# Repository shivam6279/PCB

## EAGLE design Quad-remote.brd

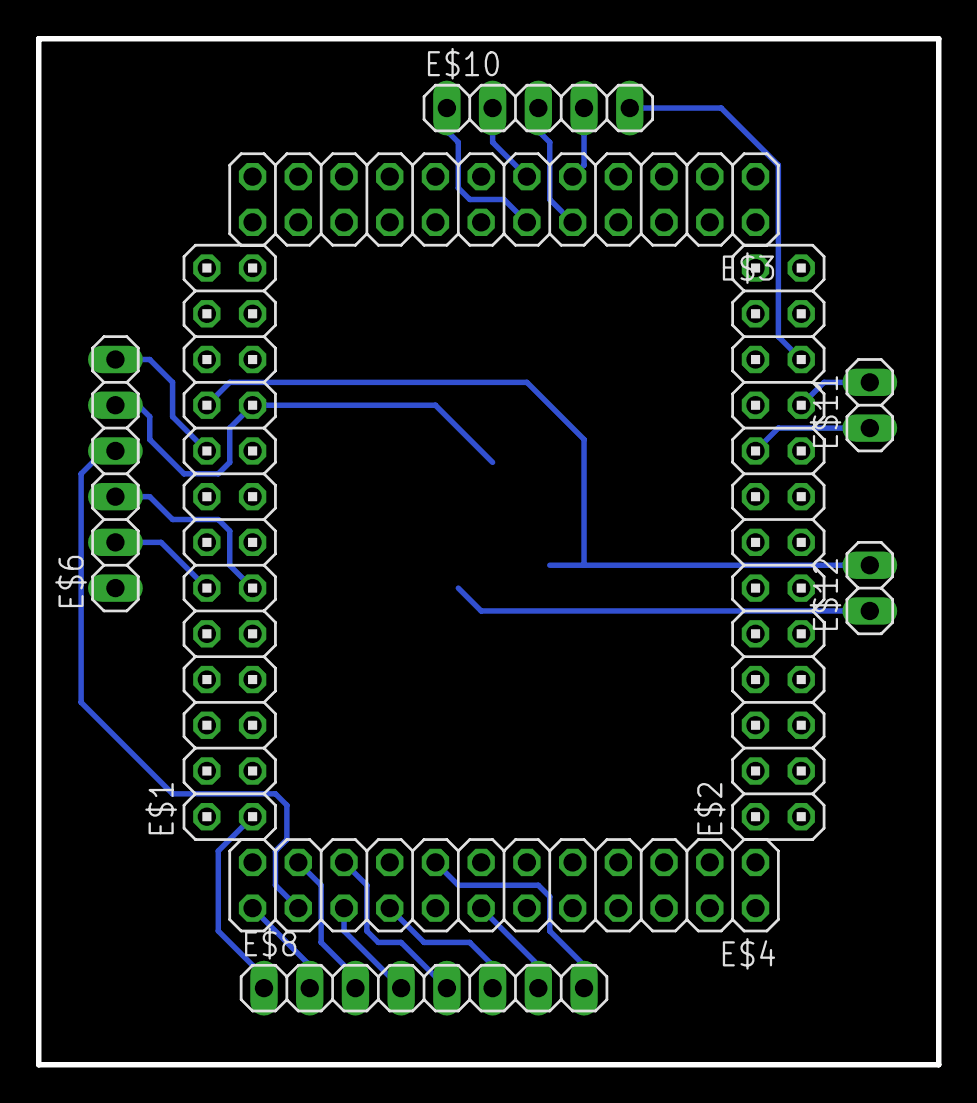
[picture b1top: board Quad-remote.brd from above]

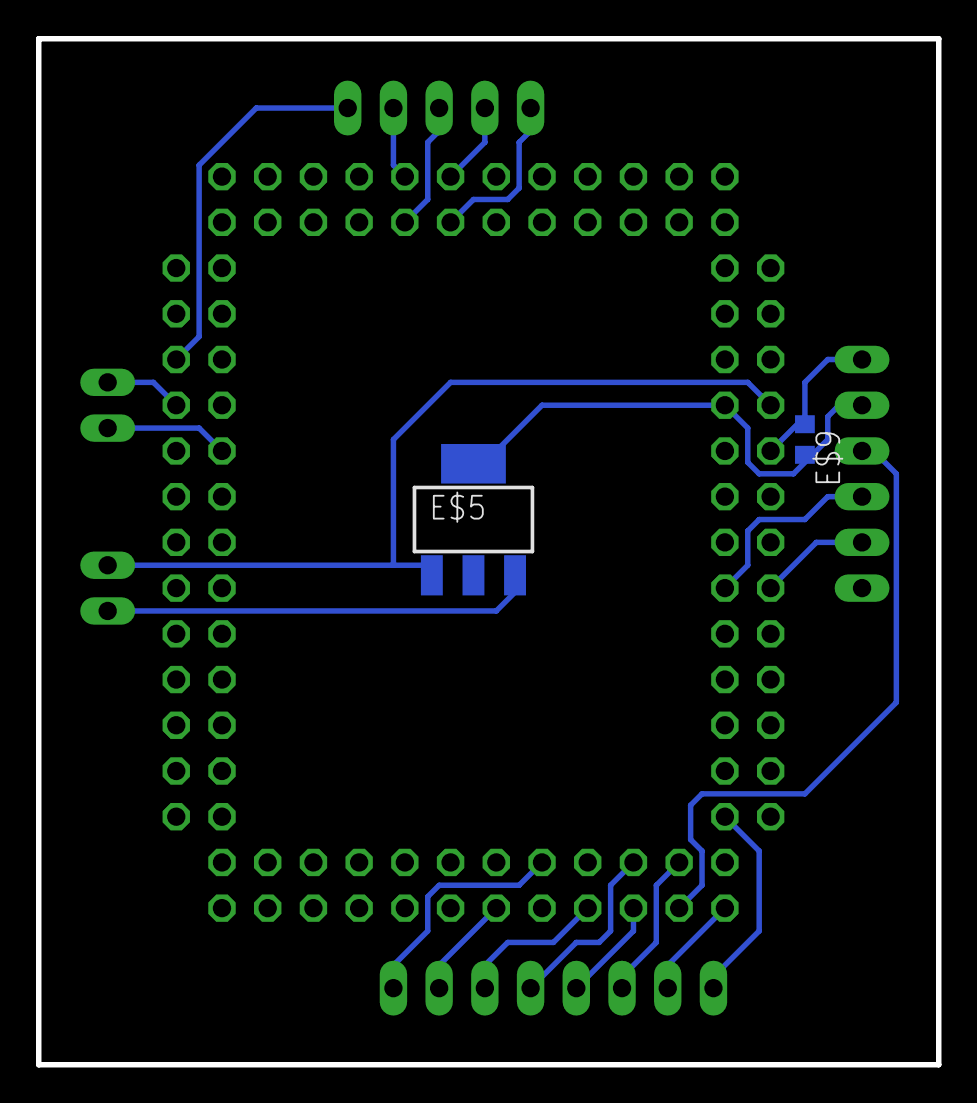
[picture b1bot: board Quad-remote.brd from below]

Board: 2 copper layers, 50.0 x 57.0 mm, 11 parts (2 on the bottom side), 20 nets.

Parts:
E$1, E$2: 2X13
E$3, E$4: 2X12
E$5: SOT223
E$6: 1X06
E$8: 1X08
E$9: R0603
E$10: 1X05
E$11, E$12: 1X02

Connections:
S$20: E$1.20, E$12.2
S$21: E$1.19, E$6.5
S$22: E$1.18, E$6.6
S$23: E$1.12, E$6.2
S$24: E$1.11, E$6.3
S$25: E$1.1, E$8.1
S$26: E$4.24, E$8.2
S$27: E$4.21, E$8.3
S$28: E$4.19, E$8.5
S$29: E$4.20, E$8.4
S$30: E$4.18, E$8.6
S$31: E$4.14, E$8.7
S$32: E$4.15, E$8.8
S$34: E$2.21, E$10.5
S$36: E$3.9, E$10.4
S$37: E$3.10, E$10.3
S$38: E$3.11, E$10.2
S$39: E$3.12, E$10.1
S$41: E$2.18, E$11.1
S$43: E$4.22, E$6.4

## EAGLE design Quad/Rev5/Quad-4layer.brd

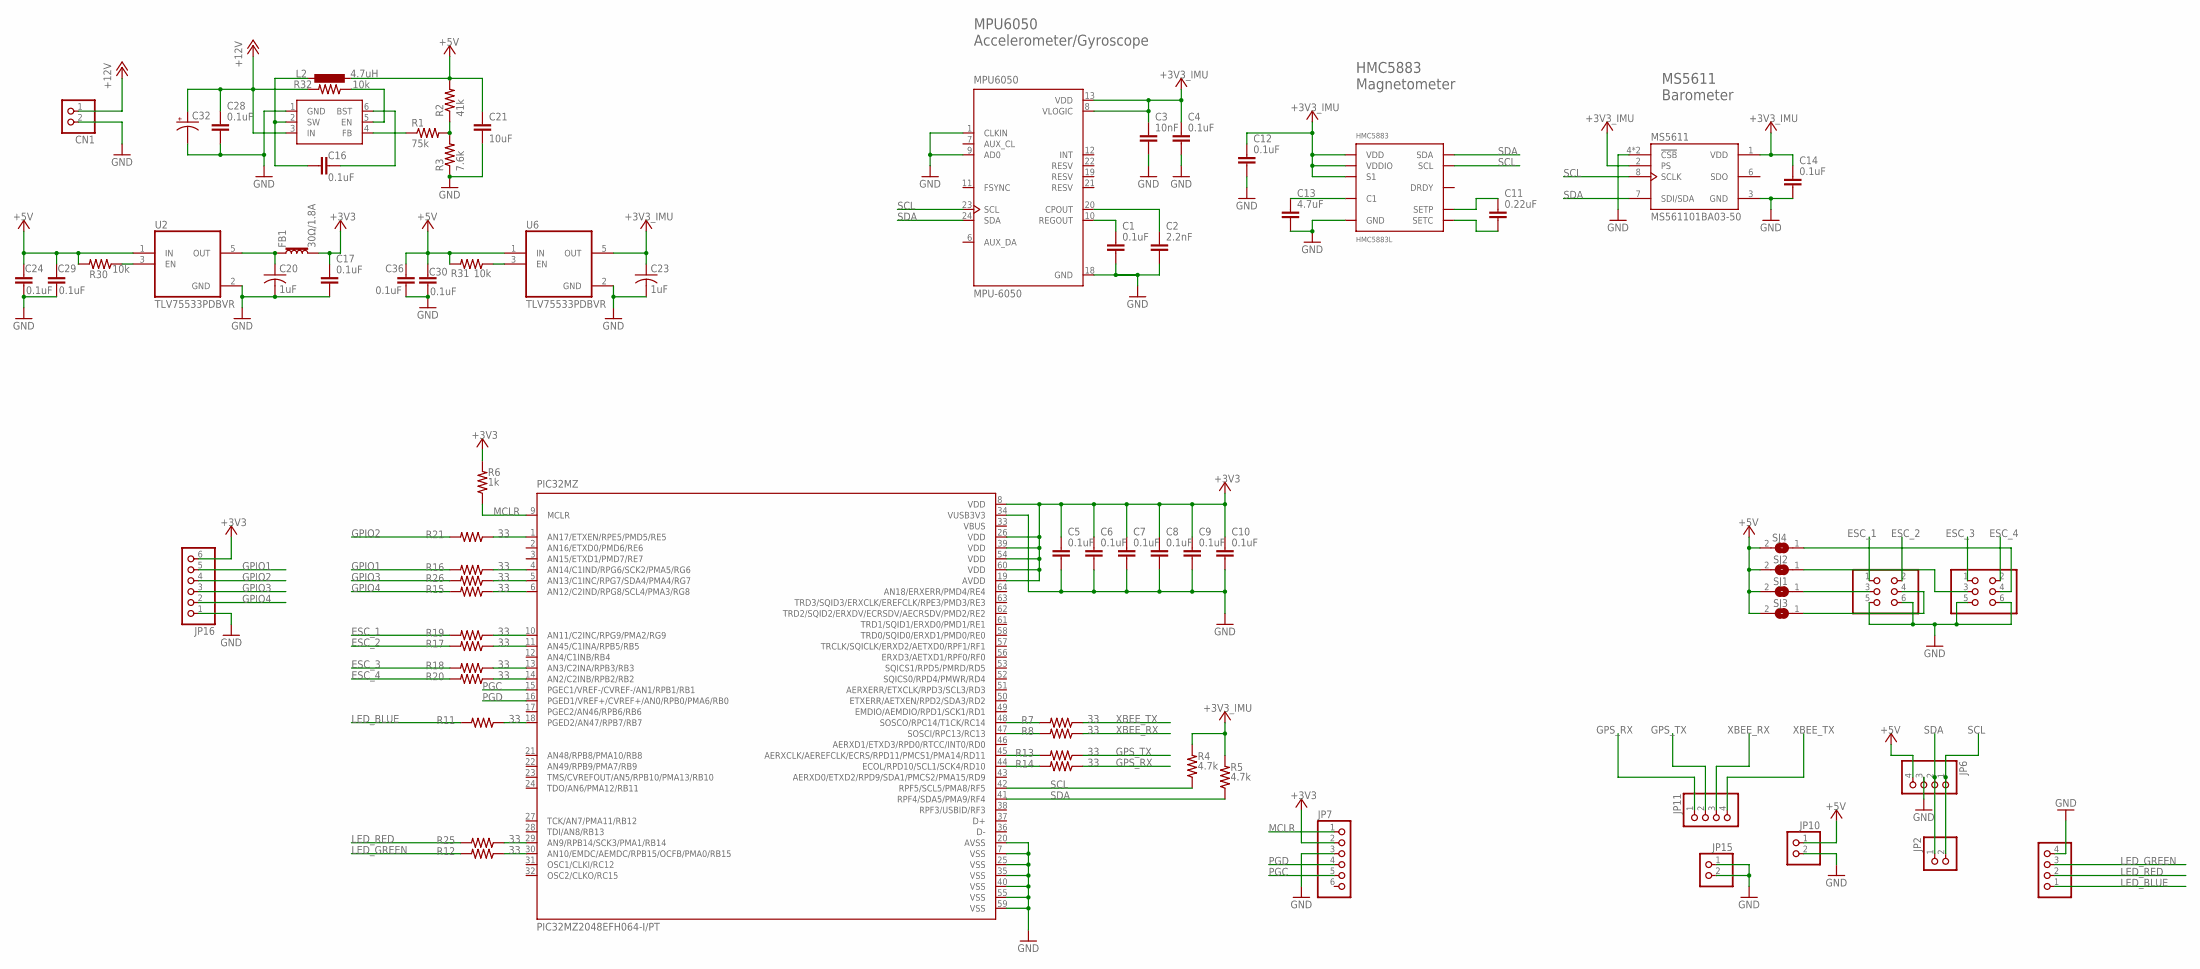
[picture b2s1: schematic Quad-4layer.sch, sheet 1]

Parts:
C1, C4, C5, C6, C7, C8, C9, C10, C12, C14, C16, C17, C24, C28, C29, C30, C36: 0.1uF; C0603
C2: 2.2nF; C0603
C3: 10nF; C0603
C11: 0.22uF; C0603
C13: 4.7uF; C0603
C20, C23: 1uF; C0805
C21: 10uF; C1206
C32: CPOL-US085CS-1AR; 085CS_1AR
CN1: JST_2PIN-THM-RA; JST-PH-2-THM-RA
FB1: 30Ω/1.8A; 0603
HMC5883: HMC5883L; LPCC-16
JP2, JP10, JP15: PINHD-1X2; 1X02
JP4, JP5: PINHD-2X3; 2X03
JP6, JP9, JP11: PINHD-1X4; 1X04
JP7, JP16: PINHD-1X6; 1X06
L2: 4.7uH; L2825P
MPU6050: MPU-6050; QFN50P400X400X95-24N
MS5611: MS561101BA03-50; SON125P500X300X100-8N
PIC32MZ: PIC32MZ2048EFH064-I/PT; QFP50P1200X1200X120-64N
R1: 75k; R0603
R2: 41k; R0603
R3: 7.6k; R0603
R4, R5: 4.7k; R0603
R6: 1k; R0603
R7, R8, R11, R12, R13, R14, R15, R16, R17, R18, R19, R20, R21, R25, R26: 33; R0603
R30, R31, R32: 10k; R0603
SJ1, SJ2, SJ3, SJ4: SJ
U2, U6: TLV75533PDBVR; SOT95P280X145-5N
U$2: AP65211A; SOT95P280X140-6N

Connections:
+3V3: C5.1, C6.1, C7.1, C8.1, C9.1, C10.1, C17.1, FB1.2, JP7.2, JP16.6, PIC32MZ.8 (VDD), PIC32MZ.19 (AVDD), PIC32MZ.26 (VDD), PIC32MZ.39 (VDD), PIC32MZ.54 (VDD), PIC32MZ.60 (VDD), R6.2
+5V: C21.1, C24.1, C29.1, C30.1, C36.1, JP6.4, JP10.1, L2.1, R2.2, R30.2, R31.2, SJ1.2, SJ2.2, SJ3.2, SJ4.2, U2.1 (IN), U6.1 (IN)
+12V: C28.1, C32.+, CN1.1 (2), R32.2, U$2.3 (IN)
ESC_1: JP5.1, R19.2
ESC_2: JP5.2, R17.2
ESC_3: JP4.1, R18.2
ESC_4: JP4.2, R20.2
GND: C1.2, C2.2, C3.2, C4.2, C5.2, C6.2, C7.2, C8.2, C9.2, C10.2, C12.2, C13.2, C14.2, C17.2, C20.2, C21.2, C23.2, C24.2, C28.2, C29.2, C30.2, C32.-, C36.2, CN1.2 (1), HMC5883.9 (GND), HMC5883.11 (GND), JP4.5, JP4.6, JP5.5, JP5.6, JP6.3, JP7.3, JP9.4, JP10.2, JP15.1, JP15.2, JP16.1, MPU6050.1 (CLKIN), MPU6050.9 (AD0), MPU6050.18 (GND), MS5611.3 (GND), MS5611.4 (!CSB), MS5611.5 (!CSB), PIC32MZ.7 (VSS), PIC32MZ.20 (AVSS), PIC32MZ.25 (VSS), PIC32MZ.34 (VUSB3V3), PIC32MZ.35 (VSS), PIC32MZ.40 (VSS), PIC32MZ.55 (VSS), PIC32MZ.59 (VSS), R3.1, U2.2 (GND), U6.2 (GND), U$2.1 (GND)
GPIO1: JP16.5, R16.2
GPIO2: JP16.4, R21.2
GPIO3: JP16.3, R26.2
GPIO4: JP16.2, R15.2
GPS_RX: JP11.1, R14.1
GPS_TX: JP11.2, R13.1
LED_BLUE: JP9.1, R11.2
LED_GREEN: JP9.3, R12.2
LED_RED: JP9.2, R25.2
MCLR: JP7.1, PIC32MZ.9 (MCLR), R6.1
unnamed: C1.1, MPU6050.10 (REGOUT)
unnamed: C2.1, MPU6050.20 (CPOUT)
unnamed: C11.1, HMC5883.8 (SETP)
unnamed: C11.2, HMC5883.12 (SETC)
unnamed: C13.1, HMC5883.10 (C1)
unnamed: C16.1, L2.2, U$2.2 (SW)
unnamed: C16.2, U$2.6 (BST)
unnamed: R1.1, U$2.4 (FB)
unnamed: R1.2, R2.1, R3.2
unnamed: PIC32MZ.48 (SOSCO/RPC14/T1CK/RC14), R7.2
unnamed: PIC32MZ.47 (SOSCI/RPC13/RC13), R8.2
unnamed: PIC32MZ.18 (PGED2/AN47/RPB7/RB7), R11.1
unnamed: PIC32MZ.45 (AERXCLK/AEREFCLK/ECRS/RPD11/PMCS1/PMA14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), R13.2
unnamed: PIC32MZ.44 (ECOL/RPD10/SCL1/SCK4/RD10), R14.2
unnamed: PIC32MZ.29 (AN9/RPB14/SCK3/PMA1/RB14), R25.1
unnamed: PIC32MZ.4 (AN14/C1IND/RPG6/SCK2/PMA5/RG6), R16.1
unnamed: PIC32MZ.1 (AN17/ETXEN/RPE5/PMD5/RE5), R21.1
unnamed: PIC32MZ.11 (AN45/C1INA/RPB5/RB5), R17.1
unnamed: PIC32MZ.13 (AN3/C2INA/RPB3/RB3), R18.1
unnamed: PIC32MZ.10 (AN11/C2INC/RPG9/PMA2/RG9), R19.1
unnamed: PIC32MZ.14 (AN2/C2INB/RPB2/RB2), R20.1
unnamed: JP4.4, SJ4.1
unnamed: PIC32MZ.5 (AN13/C1INC/RPG7/SDA4/PMA4/RG7), R26.1
unnamed: PIC32MZ.6 (AN12/C2IND/RPG8/SCL4/PMA3/RG8), R15.1
unnamed: R31.1, U6.3 (EN)
unnamed: R30.1, U2.3 (EN)
unnamed: PIC32MZ.30 (AN10/EMDC/AEMDC/RPB15/OCFB/PMA0/RB15), R12.1
unnamed: R32.1, U$2.5 (EN)
unnamed: C20.1, FB1.1, U2.5 (OUT)
unnamed: JP5.3, SJ1.1
unnamed: JP4.3, SJ2.1
unnamed: JP5.4, SJ3.1
PGC: JP7.5, PIC32MZ.15 (PGEC1/VREF-/CVREF-/AN1/RPB1/RB1)
PGD: JP7.4, PIC32MZ.16 (PGED1/VREF+/CVREF+/AN0/RPB0/PMA6/RB0)
SCL: HMC5883.1 (SCL), JP2.2, JP6.1, MPU6050.23 (SCL), MS5611.8 (SCLK), PIC32MZ.42 (RPF5/SCL5/PMA8/RF5), R4.1
SDA: HMC5883.16 (SDA), JP2.1, JP6.2, MPU6050.24 (SDA), MS5611.7 (SDI/SDA), PIC32MZ.41 (RPF4/SDA5/PMA9/RF4), R5.1
VBUS: PIC32MZ.33 (VBUS)
VCC: C3.1, C4.1, C12.1, C14.1, C23.1, HMC5883.2 (VDD), HMC5883.4 (S1), HMC5883.13 (VDDIO), MPU6050.8 (VLOGIC), MPU6050.13 (VDD), MS5611.1 (VDD), MS5611.2 (PS), R4.2, R5.2, U6.5 (OUT)
XBEE_RX: JP11.3, R8.1
XBEE_TX: JP11.4, R7.1

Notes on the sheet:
MPU6050 Accelerometer/Gyroscope
HMC5883 Magnetometer
MS5611 Barometer

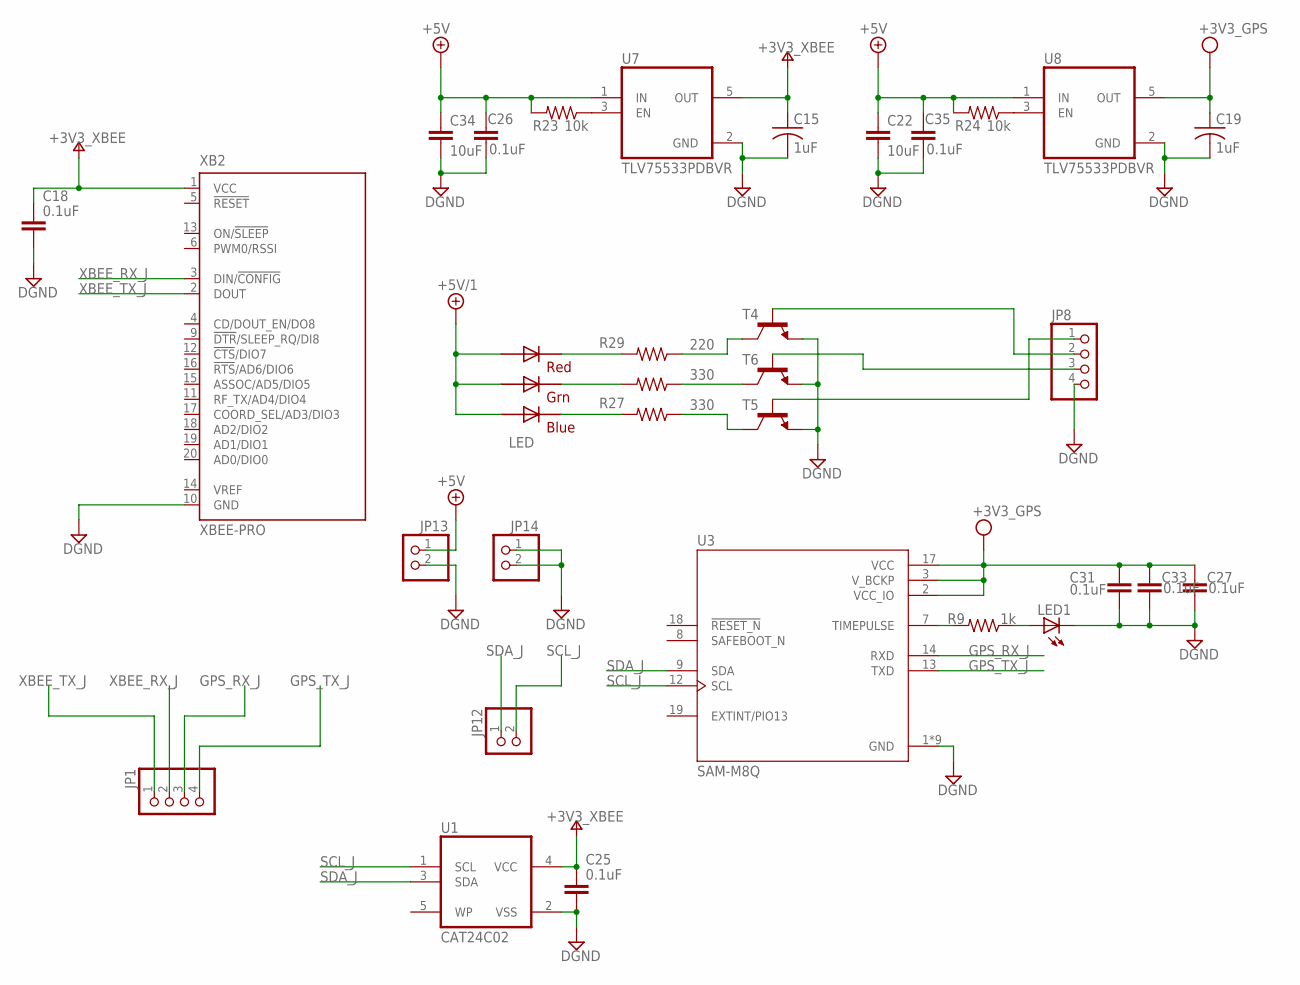
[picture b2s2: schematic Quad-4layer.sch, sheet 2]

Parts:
C15, C19: 1uF; C0805
C18, C25, C26, C27, C31, C33, C35: 0.1uF; C0603
C22, C34: 10uF; C1206
JP1, JP8: PINHD-1X4; 1X04
JP12, JP13, JP14: PINHD-1X2; 1X02
LED: RGBLED5050
LED1: LEDCHIPLED_0603; CHIPLED_0603
R9: 1k; R0603
R23, R24: 10k; R0603
R27, R28: 330; R0603
R29: 220; R0603
T4, T5, T6: -NPN-SOT23-EBC; SOT23-EBC
U1: CAT24C02; SOT95P280X145-5N
U3: SAM-M8Q; XCVR_SAM-M8Q
U7, U8: TLV75533PDBVR; SOT95P280X145-5N
XB2: XBEE-PRO

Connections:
+5V/1: C22.1, C26.1, C34.1, C35.1, JP13.1, LED.1 (GREEN_A), LED.2 (RED_A), LED.3 (BLUE_A), R23.2, R24.2, U7.1 (IN), U8.1 (IN)
DGND: C15.2, C18.2, C19.2, C22.2, C25.2, C26.2, C27.2, C31.2, C33.2, C34.2, C35.2, JP8.4, JP13.2, JP14.1, JP14.2, LED1.C, T4.E, T5.E, T6.E, U1.2 (VSS), U3.1 (GND), U3.4 (GND), U3.5 (GND), U3.6 (GND), U3.10 (GND), U3.11 (GND), U3.15 (GND), U3.16 (GND), U3.20 (GND), U7.2 (GND), U8.2 (GND), XB2.10 (GND)
GPS_RX_J: JP1.3, U3.14 (RXD)
GPS_TX_J: JP1.4, U3.13 (TXD)
LED_BLUE1: JP8.1, T5.B
LED_GREEN1: JP8.2, T4.B
unnamed: LED.5 (RED_C), R29.2
unnamed: LED.6 (GREEN_C), R28.2
unnamed: R9.2, U3.7 (TIMEPULSE)
unnamed: LED.4 (BLUE_C), R27.2
unnamed: LED1.A, R9.1
unnamed: R23.1, U7.3 (EN)
unnamed: R24.1, U8.3 (EN)
unnamed: JP8.3, T6.B
unnamed: R28.1, T6.C
unnamed: R29.1, T4.C
unnamed: R27.1, T5.C
SCL_J: JP12.2, U1.1 (SCL), U3.12 (SCL)
SDA_J: JP12.1, U1.3 (SDA), U3.9 (SDA)
V+: C15.1, C18.1, C25.1, U1.4 (VCC), U7.5 (OUT), XB2.1 (VCC)
VDD: C19.1, C27.1, C31.1, C33.1, U3.2 (VCC_IO), U3.3 (V_BCKP), U3.17 (VCC), U8.5 (OUT)
XBEE_RX_J: JP1.2, XB2.3 (DIN/!CONFIG)
XBEE_TX_J: JP1.1, XB2.2 (DOUT)

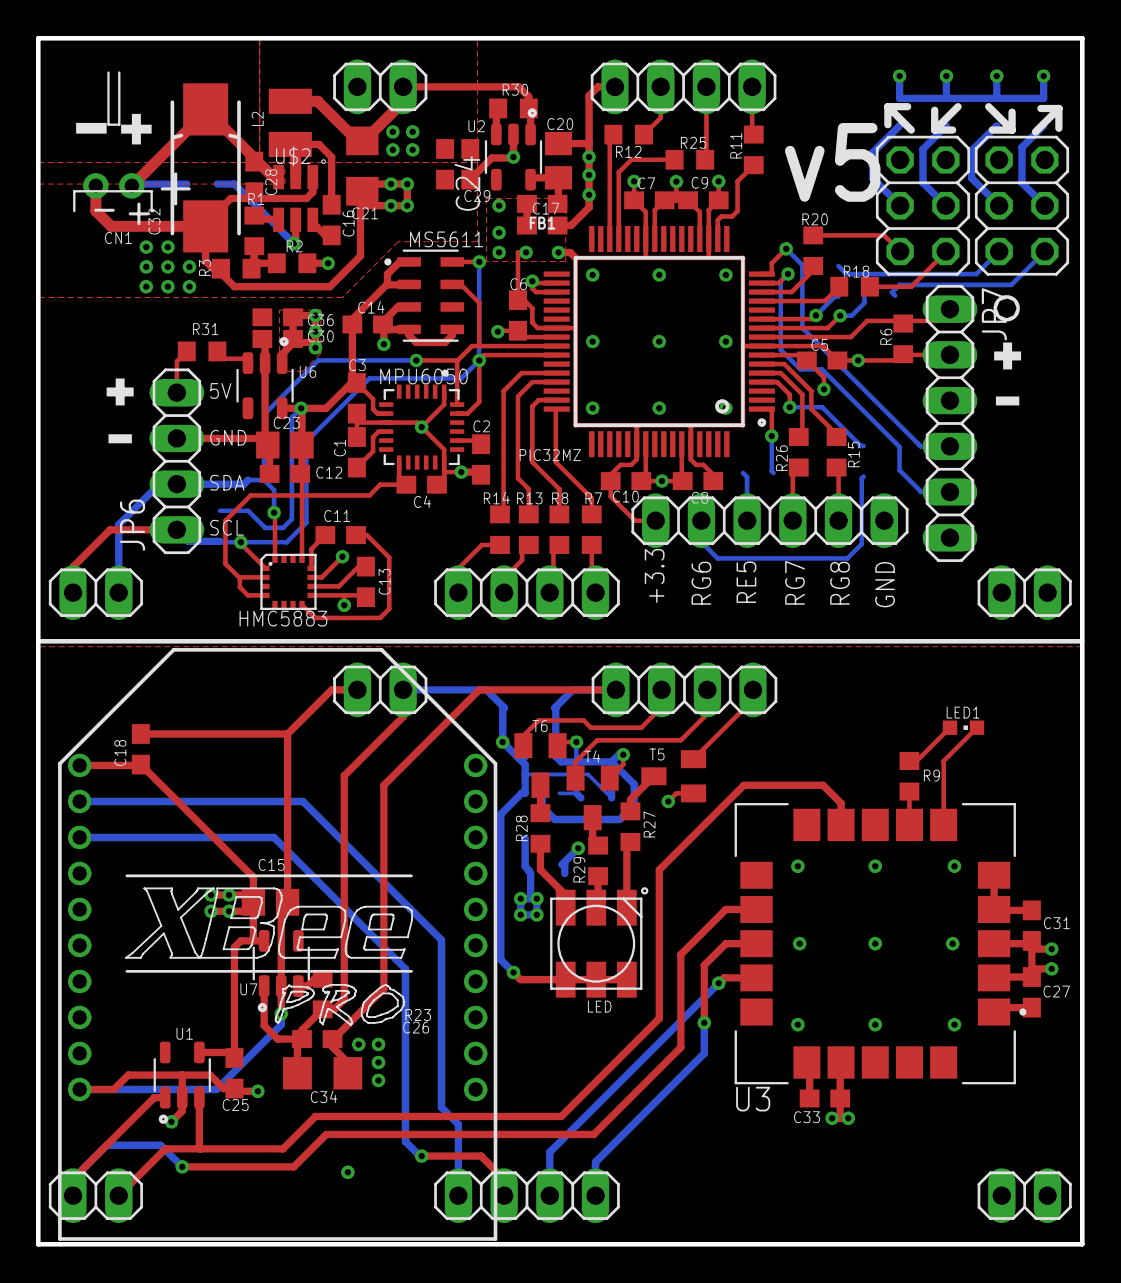
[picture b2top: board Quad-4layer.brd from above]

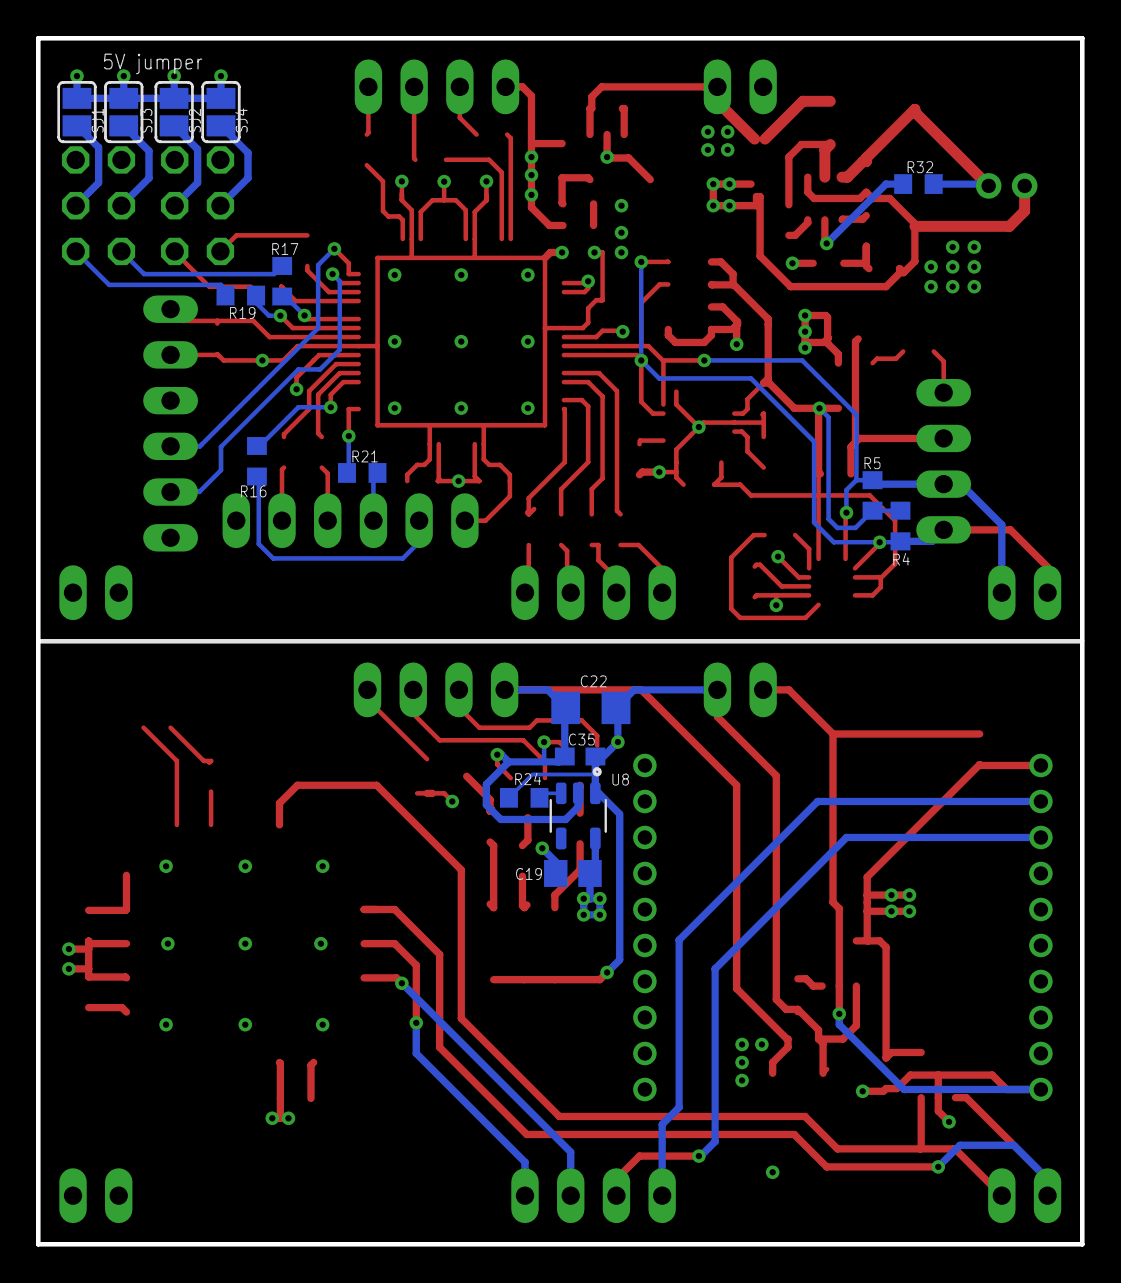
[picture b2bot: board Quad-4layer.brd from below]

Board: 4 copper layers, 58.0 x 67.0 mm, 105 parts (16 on the bottom side), 80 nets.

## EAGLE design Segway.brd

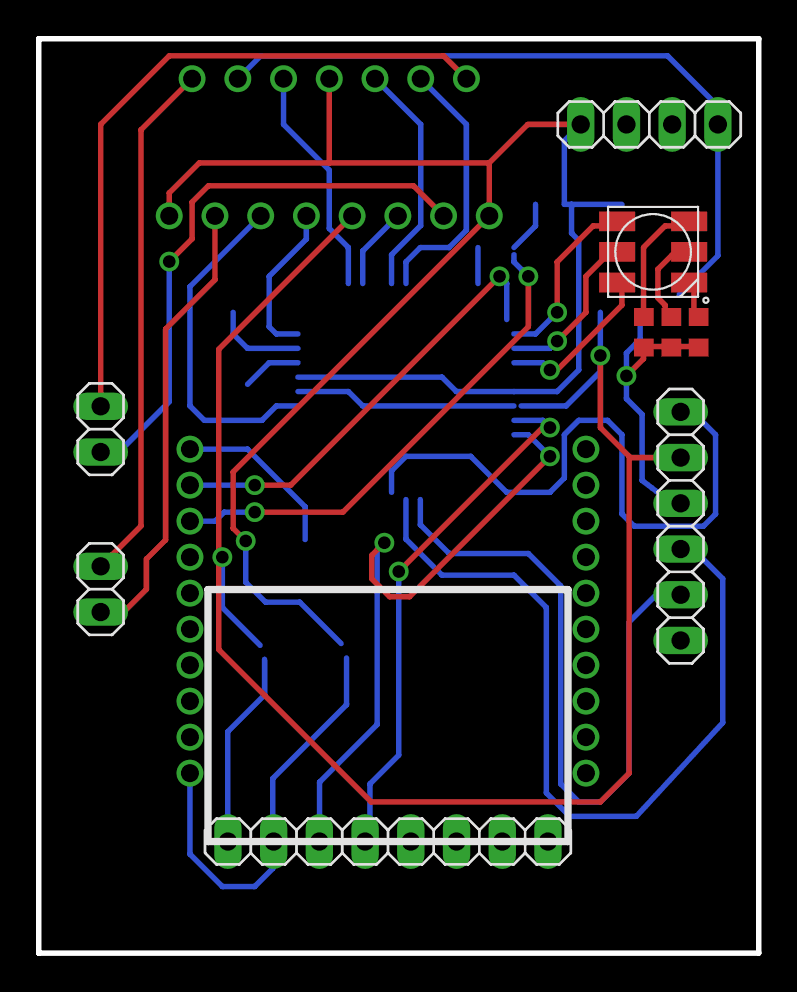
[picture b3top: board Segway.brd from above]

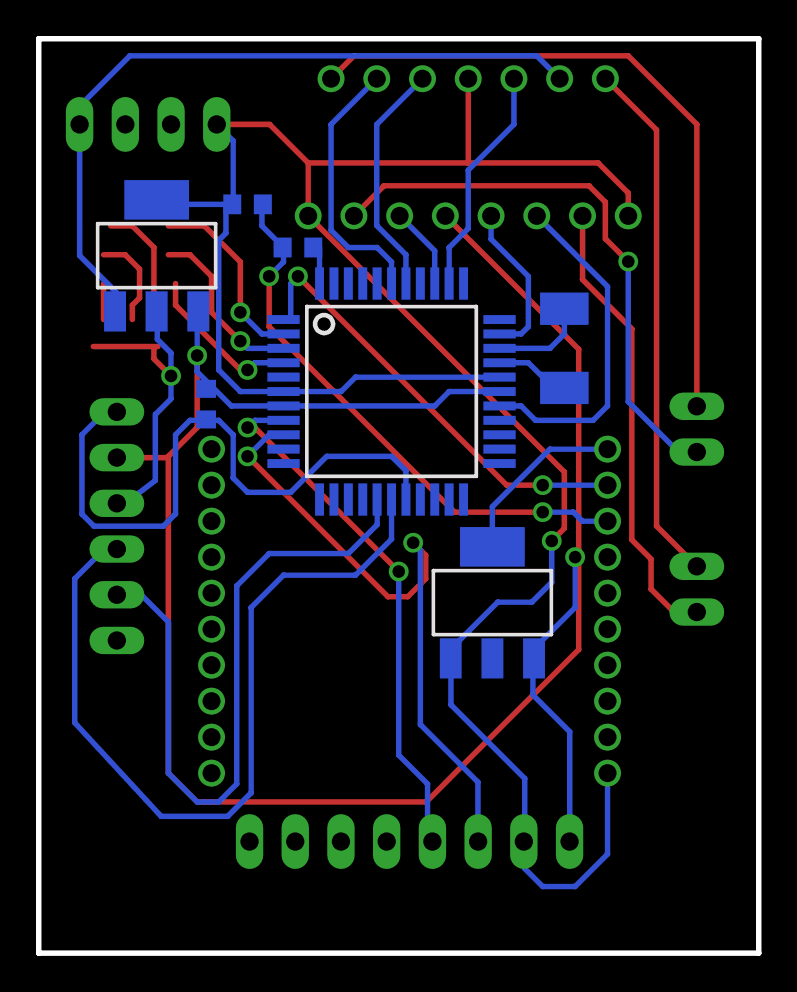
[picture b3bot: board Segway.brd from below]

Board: 2 copper layers, 40.0 x 50.8 mm, 16 parts (7 on the bottom side), 5 nets.

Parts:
E$1: SQFP-S-10X10-44
E$2: RGBLED5050
E$3: 1X06
E$4, E$10: SOT223
E$5, E$7, E$9, E$13, E$14, E$15: R0603
E$6: R2010
E$8: 1X04
E$11, E$12: 1X02
E$16: 1X08

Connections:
S$23: E$1.7, E$1.28
S$29: E$1.17, E$3.3
S$30: E$1.16, E$3.2
S$35: E$1.6, E$1.29, E$8.1
S$41: E$1.2, E$1.3, E$1.4

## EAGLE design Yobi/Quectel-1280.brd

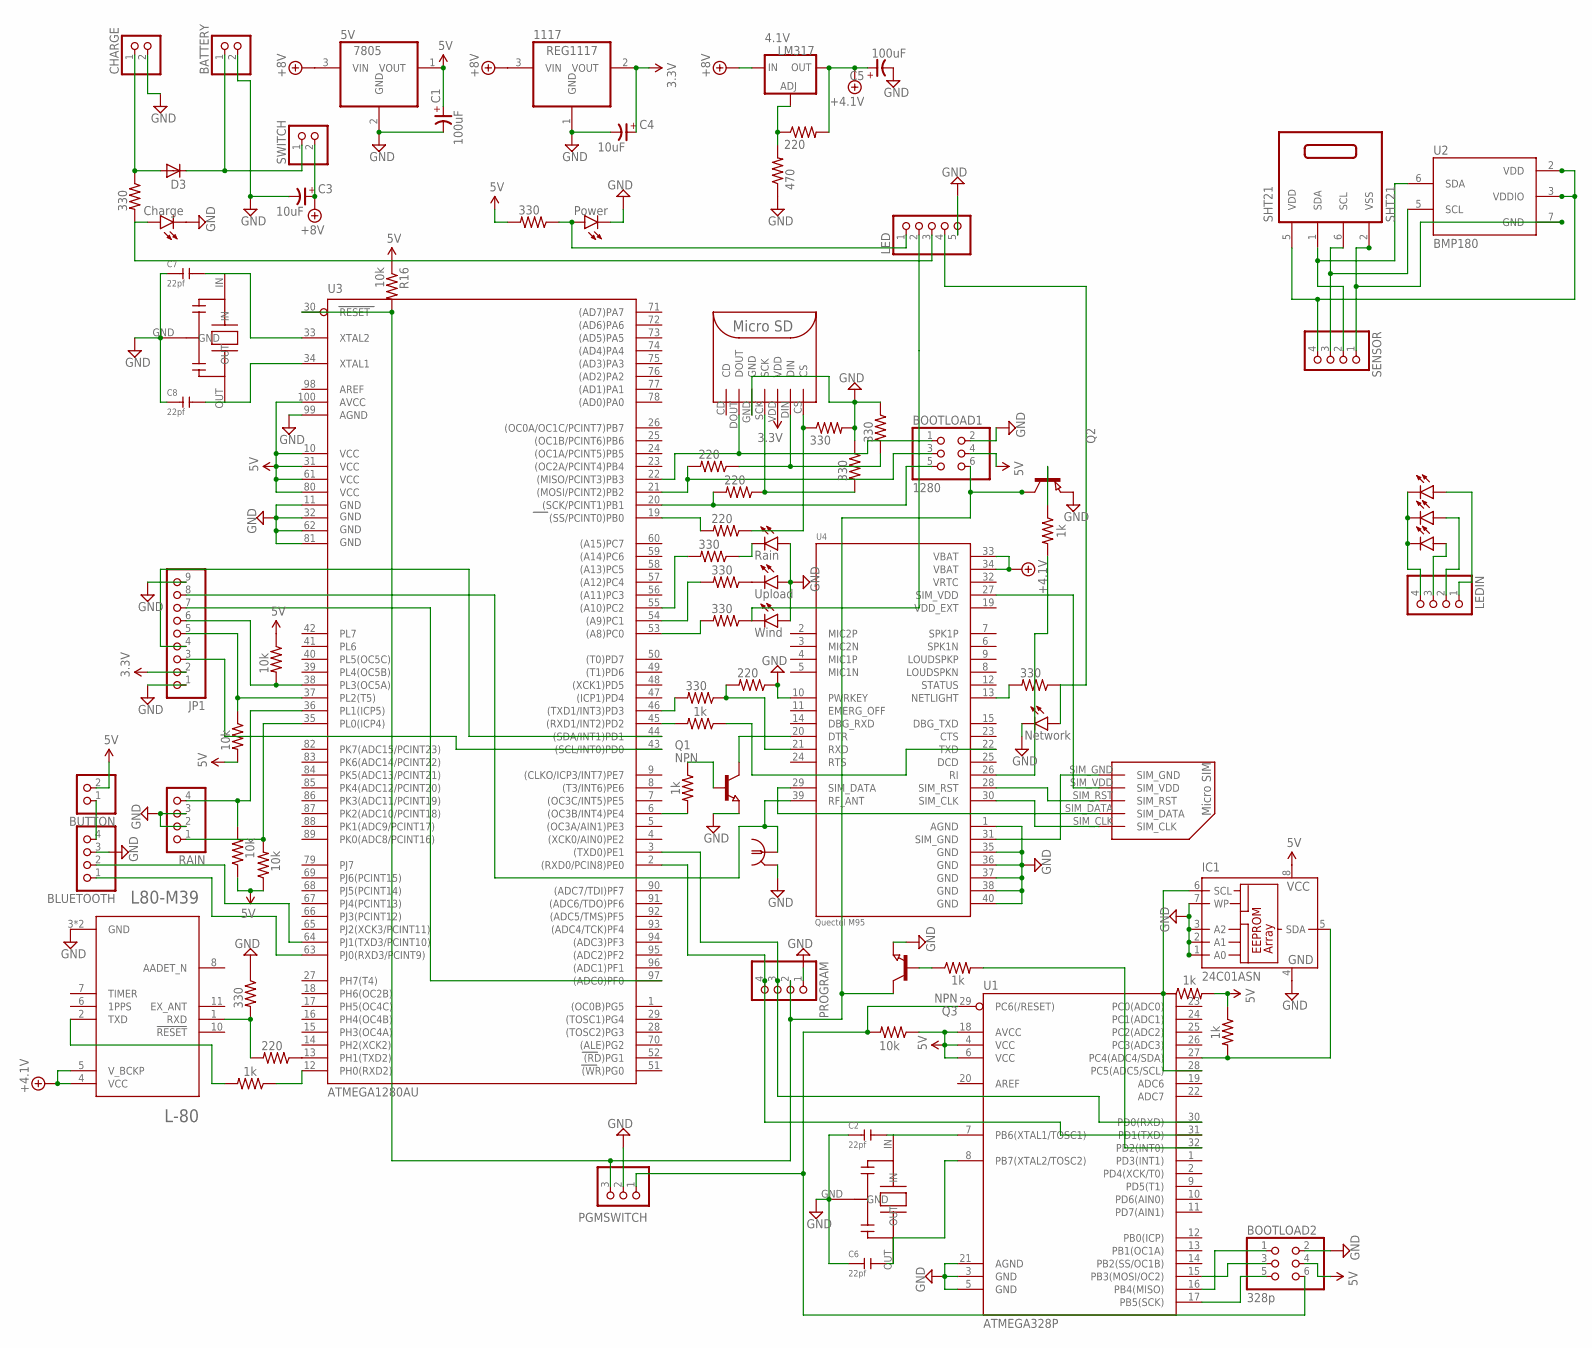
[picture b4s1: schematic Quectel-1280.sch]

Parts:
4.1V: LM317; DPACK
5V: 7805; SOT223; MPN 7805
1117: REG1117; SOT223
ANT: LTI-SASF54GT
BATTERY: PINHD-1X2; 1X02
BLUETOOTH: PINHD-1X4; 1X04
BOOTLOAD1: 1280; 2X03
BOOTLOAD2: 328p; 2X03
BUTTON: PINHD-1X2; 1X02
C1, C5: 100uF; 3528/T
C2, C6, C7, C8: 22pf; C0805
C3, C4: 10uF; 3528/T
CHARGE: PINHD-1X2; 1X02
D1: Charge; LED-1206
D2: Rain; LED-1206
D3: BYS10; SOD106A
D4: Upload; LED-1206
D5: Power; LED-1206
D6: Network; LED-1206
D7: Wind; LED-1206
D8, D9, D10: LED-BLUE1206; LED-1206
IC1: 24C01ASN; SO-08
JP1: PINHD-1X9; 1X09
L-80: L80-M39; QUECTEL_L80-M39
LED: PINHD-1X5; 1X05
LEDIN: PINHD-1X4; 1X04
PGMSWITCH: PINHD-1X3; 1X03
PROGRAM: PINHD-1X4; 1X04
Q1, Q3: NPN; SOT23
Q2: PNP-TRANSISTOR_SOT23; SOT23
R1, R16, R19, R20, R21, R22: 10k; 0805
R2, R3, R5, R13, R15, R30, R31: 1k; 0805
R4, R9, R14, R17, R18, R23, R24, R25, R26, R27, R28: 330; 0805
R6, R7, R8, R10, R12, R29: 220; 0805
R11: 470; 0805
RAIN: PINHD-1X4; 1X04
SENSOR: PINHD-1X4; 1X04
SHT21: SHT21; DFN6/SHT
SWITCH: PINHD-1X2; 1X02
U1: ATMEGA328P; TQFP32-08
U2: BMP180
U3: ATMEGA1280AU; TQFP100
U4: Quectel M95; XCVR_M95
U$1: MICROSD
U$2: MICROSIM
Y1, Y2: CSTCE16M0V53-R0; CFP95P160X100-3N

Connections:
3.3V: 1117.2 (VOUT), C4.+, JP1.2, U$1.VDD
5V: 5V.1 (VOUT), BOOTLOAD1.4, BOOTLOAD2.4, BUTTON.2, C1.+, IC1.8 (VCC), R1.1, R5.1, R16.1, R18.2, R19.1, R20.2, R21.1, R22.1, R30.2, U1.4 (VCC), U1.6 (VCC), U1.18 (AVCC), U3.10 (VCC), U3.31 (VCC1), U3.61 (VCC2), U3.80 (VCC3), U3.100 (AVCC)
+4.1V: 4.1V.4 (OUT), C5.+, L-80.4 (VCC), L-80.5 (V_BCKP), R10.2, U4.33 (VBAT), U4.34 (VBAT)
+8V: 4.1V.3 (IN), 5V.3 (VIN), 1117.3 (VIN), C3.+, SWITCH.2
GND: 5V.2 (GND), 1117.1 (GND), ANT.2, ANT.3 (2), ANT.4 (2), ANT.5 (2), BATTERY.2, BLUETOOTH.3, BOOTLOAD1.2, BOOTLOAD2.2, C1.-, C2.1, C3.-, C4.-, C5.-, C6.1, C7.1, C8.1, CHARGE.2, D1.C, D2.A, D4.A, D5.C, D6.C, D7.A, IC1.1 (A0), IC1.2 (A1), IC1.3 (A2), IC1.4 (GND), IC1.7 (WP), JP1.1, JP1.9, L-80.3 (GND), L-80.12 (GND), LED.5, PGMSWITCH.2, PROGRAM.1, Q1.2 (E), Q2.2 (E), Q3.2 (E), R4.1, R9.1, R11.1, R23.2, R24.1, R29.1, RAIN.2, RAIN.3, U1.3 (GND), U1.5 (GND), U1.21 (AGND), U3.11 (GND), U3.32 (GND1), U3.62 (GND2), U3.81 (GND3), U3.99 (AGND), U4.1 (AGND), U4.10 (PWRKEY), U4.35 (GND), U4.36 (GND), U4.37 (GND), U4.38 (GND), U4.40 (GND), U$1.GND, Y1.GND, Y2.GND
GNDLED: D8.C, D9.C, D10.C, LEDIN.4
GNDSENSOR: SENSOR.1, SHT21.2 (VSS), U2.7 (GND)
unnamed: U4.31 (SIM_GND), U$2.SIM_GND
unnamed: U4.27 (SIM_VDD), U$2.SIM_VDD
unnamed: U4.28 (SIM_RST), U$2.SIM_RST
unnamed: U4.29 (SIM_DATA), U$2.SIM_DATA
unnamed: ANT.1, JP1.8, U4.39 (RF_ANT)
unnamed: U4.30 (SIM_CLK), U$2.SIM_CLK
unnamed: L-80.2 (TXD), R13.2
unnamed: PROGRAM.4, U1.31 (PD1(TXD)), U3.2 ((RXD0/PCIN8)PE0)
unnamed: PROGRAM.3, U1.30 (PD0(RXD)), U3.3 ((TXD0)PE1)
unnamed: R7.1, R24.2, U$1.SCK
unnamed: BOOTLOAD1.1, U3.22 ((MISO/PCINT3)PB3), U$1.DOUT
unnamed: R6.1, R9.2, U$1.DIN
unnamed: C2.2, U1.7 (PB6(XTAL1/TOSC1)), Y1.IN
unnamed: R2.2, U3.6 ((OC3B/INT4)PE4)
unnamed: Q1.1 (B), R2.1
unnamed: BOOTLOAD1.3, R6.2, U3.21 ((MOSI/PCINT2)PB2)
unnamed: BOOTLOAD1.5, R7.2, U3.20 ((SCK/PCINT1)PB1)
unnamed: R3.2, U4.26 (RI)
unnamed: BATTERY.1, D3.K, SWITCH.1
unnamed: R8.2, U3.19 ((SS/PCINT0)PB0)
unnamed: BOOTLOAD2.1, U1.16 (PB4(MISO))
unnamed: BOOTLOAD2.3, U1.15 (PB3(MOSI/OC2))
unnamed: BOOTLOAD2.5, U1.17 (PB5(SCK))
unnamed: C6.2, U1.8 (PB7(XTAL2/TOSC2)), Y1.OUT
unnamed: CHARGE.1, D3.A, R26.1
unnamed: BOOTLOAD2.6, PGMSWITCH.1, R1.2, U1.29 (PC6(/RESET))
unnamed: D1.A, LED.3, R26.2
unnamed: Q2.1 (B), R3.1
unnamed: 4.1V.1 (ADJ), R10.1, R11.2
unnamed: C7.2, U3.33 (XTAL2), Y2.IN
unnamed: C8.2, U3.34 (XTAL1), Y2.OUT
unnamed: D7.C, LED.2, R28.1
unnamed: D4.C, R25.1
unnamed: D2.C, R27.1
unnamed: R8.1, R23.1, U$1.CS
unnamed: R12.1, U3.13 (PH1(TXD2))
unnamed: R13.1, U3.12 (PH0(RXD2))
unnamed: L-80.1 (RXD), R4.2, R12.2
unnamed: R28.2, U3.53 ((A8)PC0)
unnamed: R14.2, U3.46 ((TXD1/INT3)PD3)
unnamed: R15.2, U3.45 ((RXD1/INT2)PD2)
unnamed: R14.1, R29.2, U4.21 (RXD)
unnamed: R15.1, U4.22 (TXD)
unnamed: IC1.5 (SDA), R5.2, U1.27 (PC4(ADC4/SDA))
unnamed: R25.2, U3.54 ((A9)PC1)
unnamed: Q1.3 (C), U4.20 (DTR)
unnamed: BOOTLOAD1.6, PGMSWITCH.3, PROGRAM.2, Q2.3 (C), Q3.3 (C), R16.2, U3.30 (RESET)
unnamed: R27.2, U3.55 ((A10)PC2)
unnamed: IC1.6 (SCL), R30.1, U1.28 (PC5(ADC5/SCL))
unnamed: R17.2, U4.13 (NETLIGHT)
unnamed: D6.A, LED.4, R17.1
unnamed: Q3.1 (B), R31.1
unnamed: JP1.3, U3.43 ((SCL/INT0)PD0)
unnamed: JP1.4, U3.44 ((SDA/INT1)PD1)
unnamed: JP1.5, R20.1, U3.37 (PL2(T5))
unnamed: JP1.6, R19.2, U3.38 (PL3(OC5A))
unnamed: JP1.7, U3.97 ((ADC0)PF0)
unnamed: R21.2, RAIN.4, U3.36 (PL1(ICP5))
unnamed: R22.2, RAIN.1, U3.35 (PL0(ICP4))
unnamed: D5.A, LED.1, R18.1
unnamed: R31.2, U1.32 (PD2(INT0))
unnamed: BLUETOOTH.2, U3.64 (PJ1(TXD3/PCINT10))
unnamed: SENSOR.2, SHT21.1 (SDA), U2.6 (SDA)
unnamed: SENSOR.3, SHT21.6 (SCL), U2.5 (SCL)
unnamed: SENSOR.4, SHT21.5 (VDD), U2.2 (VDD), U2.3 (VDDIO)
unnamed: BLUETOOTH.1, U3.63 (PJ0(RXD3/PCINT9))
unnamed: D10.A, LEDIN.3
unnamed: D8.A, LEDIN.2
unnamed: D9.A, LEDIN.1
unnamed: BLUETOOTH.4, BUTTON.1
VDD_EXT: U4.19 (VDD_EXT)
VRTC: U4.32 (VRTC)

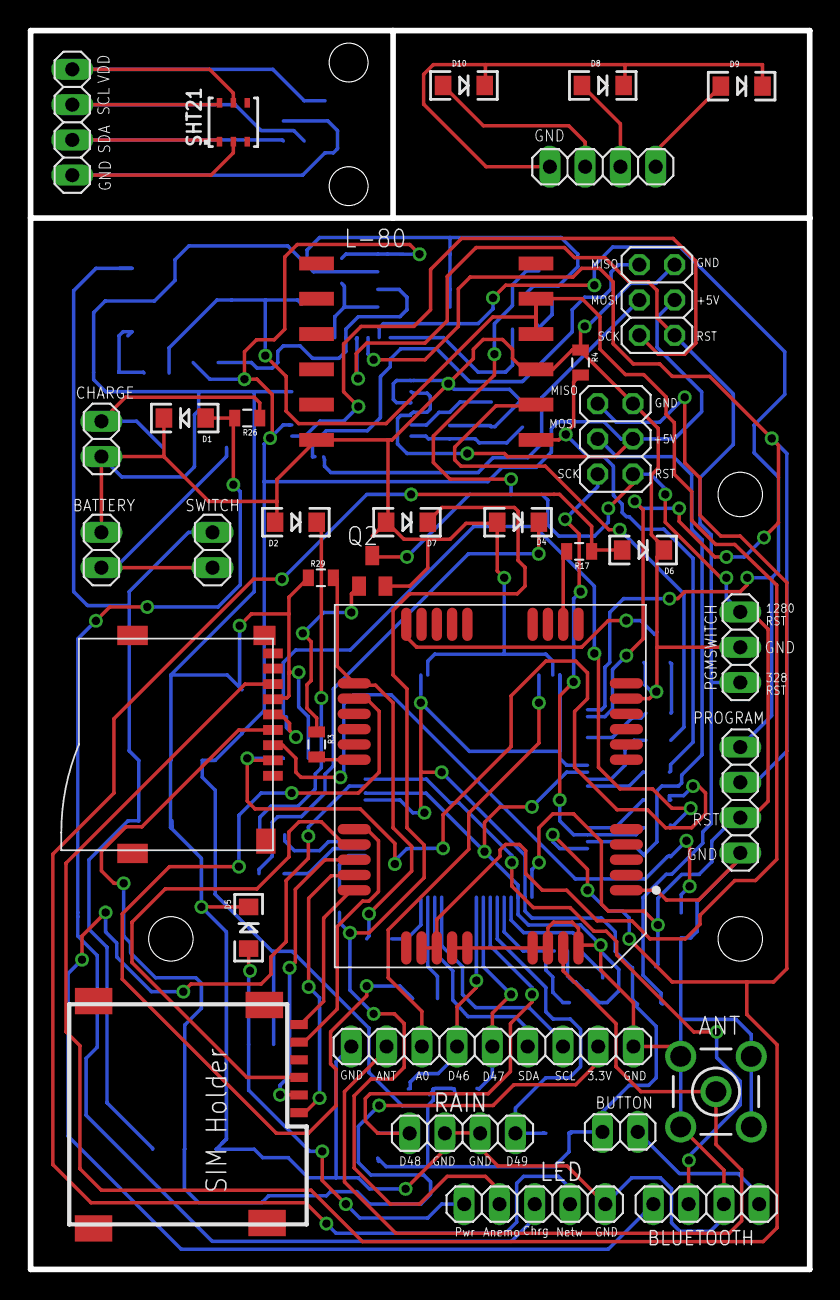
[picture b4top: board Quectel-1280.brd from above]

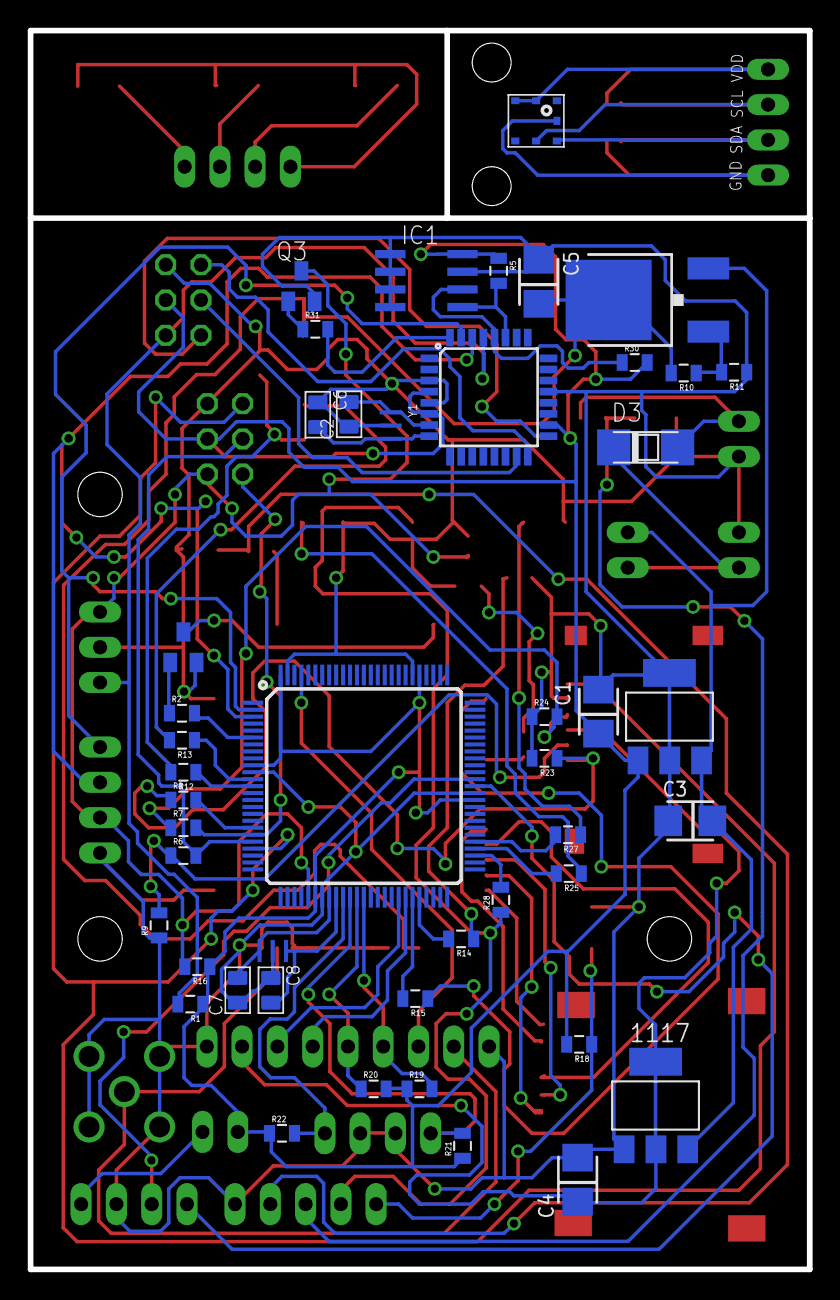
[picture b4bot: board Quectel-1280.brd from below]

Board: 2 copper layers, 56.1 x 89.2 mm, 81 parts (46 on the bottom side), 77 nets.

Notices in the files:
parts and their libraries:
SparkFun-Coils: Licensing: Creative Commons ShareAlike 4.0 International - https://creativecommons.org/licenses/by-sa/4.0
sensirion: Copyright (C) 2011, Bob Starr
